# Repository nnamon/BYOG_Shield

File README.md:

# BYOG_Shield
Resources pertaining to the Build Your Own Arduino Shield workshop conducted by [AIS Cube](http://www.aiscube.com) and organised with [12Geeks](https://12geeks.com)

>Follow us on [Facebook](https://www.facebook.com/aiscube.sg)/[Instagram](https://www.instagram.com/aiscube.sg)/[Twitter](https://twitter.com/AIS_Cube) for upcoming public workshops & photos of those we conducted.

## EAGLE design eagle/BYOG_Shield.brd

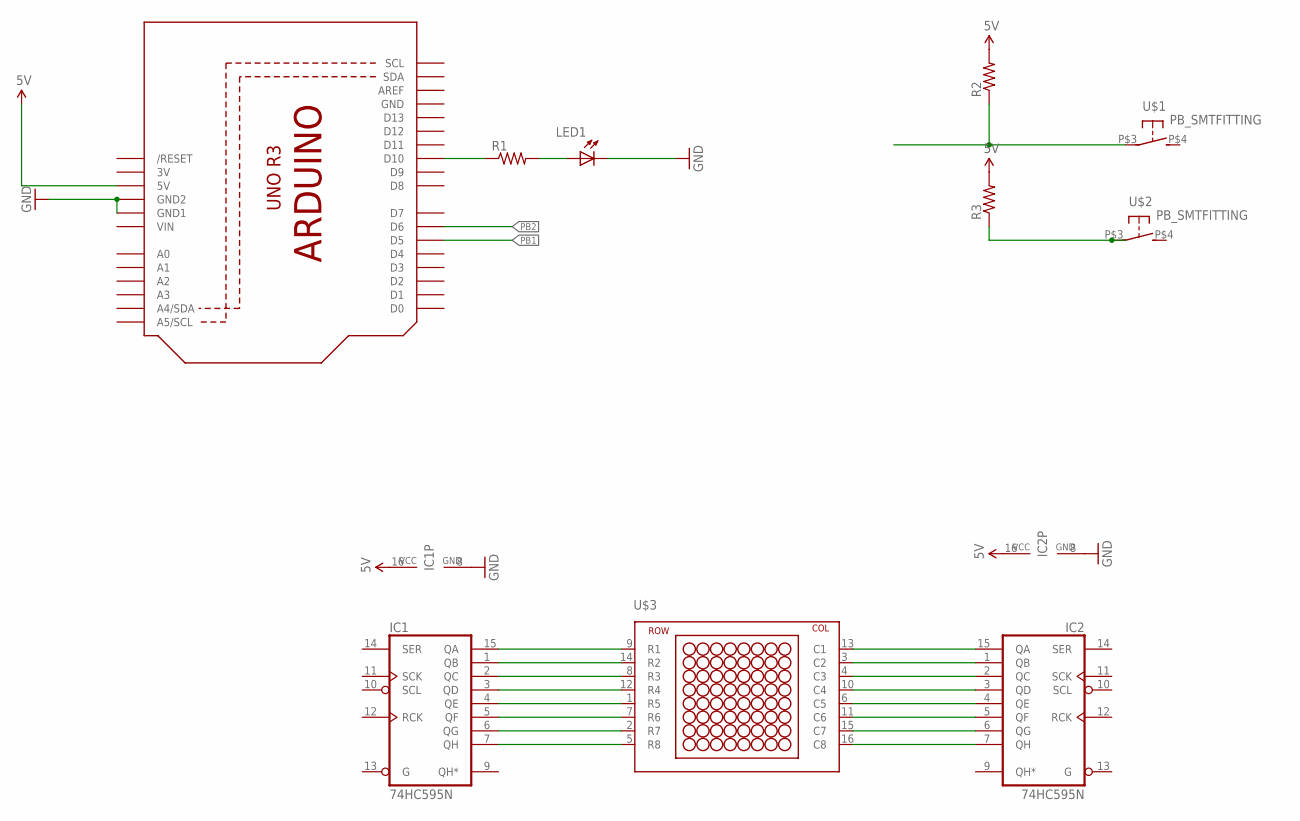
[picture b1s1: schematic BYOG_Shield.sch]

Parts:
IC1, IC2: 74HC595N; DIL16
LED1: LED/0805; CHIP-LED0805
R1, R2, R3: RESISTOR0805-RES; 0805
U1: ARDUINOR3-NOIOREF-NOTEXT; ARDUINOR3-NOTEXT-NOIOREF
U$1, U$2: PB_SMTFITTING; PB_SMT_TIGHT
U$3: 8X8DM_2088AS

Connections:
3V: U1.3V
5V: IC1.16 (VCC), IC2.16 (VCC), R2.2, R3.2, U1.5V
GND: IC1.8 (GND), IC2.8 (GND), LED1.C, U1.GND, U1.GND1, U1.GND2
unnamed: R1.1, U1.D10
unnamed: LED1.A, R1.2
unnamed: R2.1, U$1.P$3 (1)
unnamed: R3.1, U$2.P$3 (1)
unnamed: IC1.1 (QB), U$3.14 (R2)
unnamed: IC1.2 (QC), U$3.8 (R3)
unnamed: IC1.3 (QD), U$3.12 (R4)
unnamed: IC1.4 (QE), U$3.1 (R5)
unnamed: IC1.5 (QF), U$3.7 (R6)
unnamed: IC1.6 (QG), U$3.2 (R7)
unnamed: IC1.7 (QH), U$3.5 (R8)
unnamed: IC1.15 (QA), U$3.9 (R1)
unnamed: IC2.1 (QB), U$3.3 (C2)
unnamed: IC2.2 (QC), U$3.4 (C3)
unnamed: IC2.3 (QD), U$3.10 (C4)
unnamed: IC2.4 (QE), U$3.6 (C5)
unnamed: IC2.5 (QF), U$3.11 (C6)
unnamed: IC2.6 (QG), U$3.15 (C7)
unnamed: IC2.7 (QH), U$3.16 (C8)
unnamed: IC2.15 (QA), U$3.13 (C1)
PB1: U1.D5
PB2: U1.D6
VIN: U1.VIN

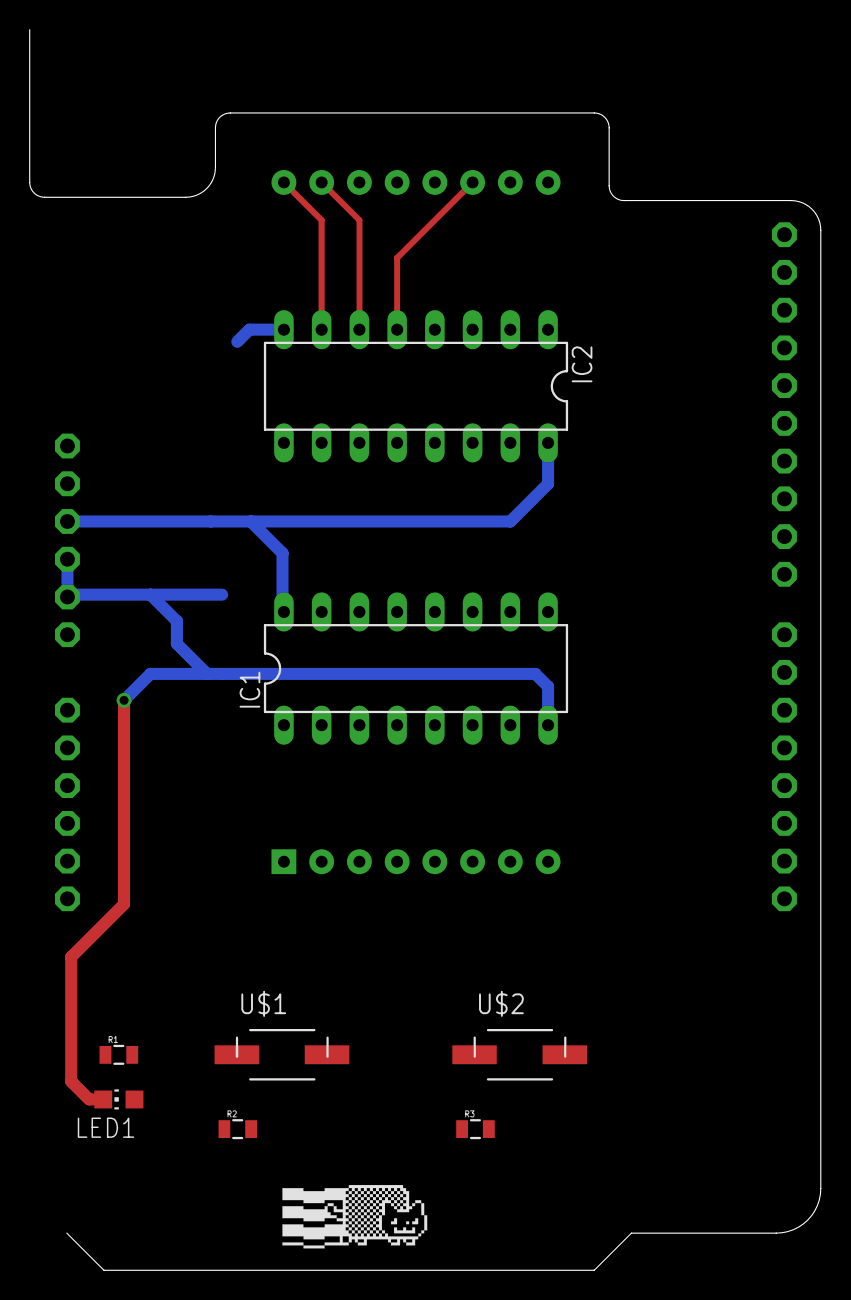
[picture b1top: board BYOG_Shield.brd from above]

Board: 2 copper layers, 53.2 x 83.5 mm, 11 parts (0 on the bottom side), 22 nets.

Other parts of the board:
U$8: LOGO_NYAN

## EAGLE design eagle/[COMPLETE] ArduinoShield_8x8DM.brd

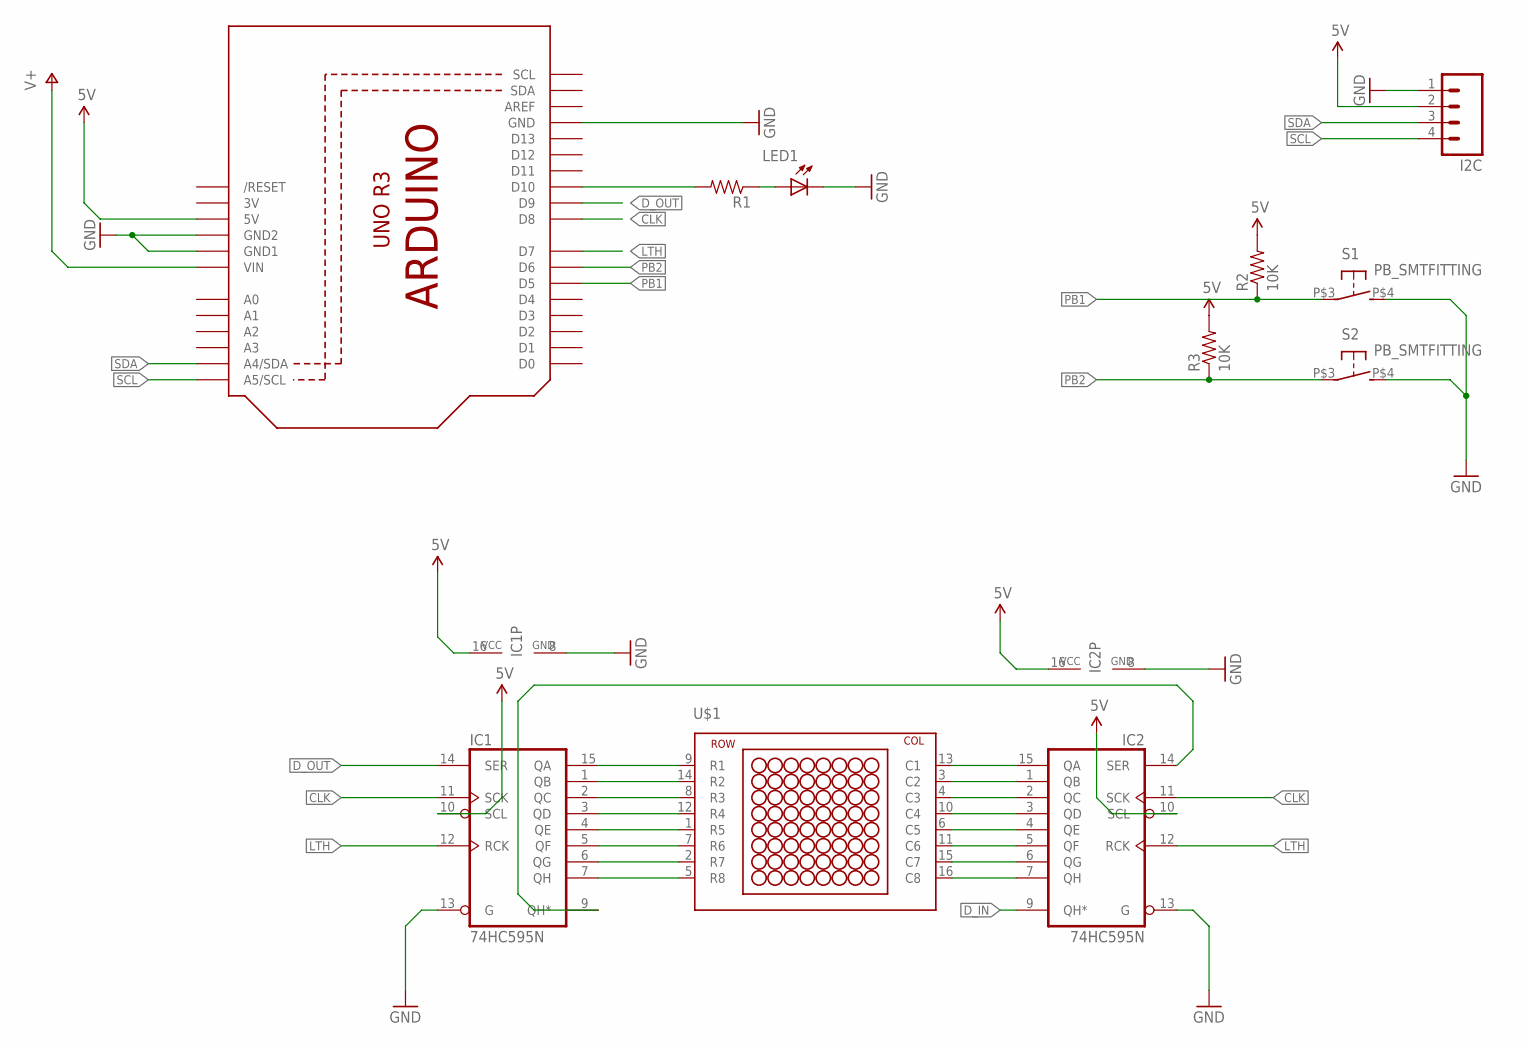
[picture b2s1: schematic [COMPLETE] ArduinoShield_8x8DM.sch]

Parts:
I2C: M04PTH; 1X04
IC1, IC2: 74HC595N; DIL16
LED1: LED/0805; CHIP-LED0805
R1: RESISTOR0805-RES; 0805
R2, R3: 10K; 0805
S1, S2: PB_SMTFITTING; PB_SMT_TIGHT
U1: ARDUINOR3-NOIOREF-NOTEXT; ARDUINOR3-NOTEXT-NOIOREF
U$1: 8X8DM_2088AS

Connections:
3V: U1.3V
5V: I2C.2, IC1.10 (SCL), IC1.16 (VCC), IC2.10 (SCL), IC2.16 (VCC), R2.2, R3.2, U1.5V
CLK: IC1.11 (SCK), IC2.11 (SCK), U1.D8
D_IN: IC2.9 (QH*)
D_OUT: IC1.14 (SER), U1.D9
GND: I2C.1, IC1.8 (GND), IC1.13 (G), IC2.8 (GND), IC2.13 (G), LED1.C, S1.P$4 (2), S2.P$4 (2), U1.GND, U1.GND1, U1.GND2
LTH: IC1.12 (RCK), IC2.12 (RCK), U1.D7
unnamed: IC1.1 (QB), U$1.14 (R2)
unnamed: IC1.2 (QC), U$1.8 (R3)
unnamed: IC1.3 (QD), U$1.12 (R4)
unnamed: IC1.4 (QE), U$1.1 (R5)
unnamed: IC1.5 (QF), U$1.7 (R6)
unnamed: IC1.6 (QG), U$1.2 (R7)
unnamed: IC1.7 (QH), U$1.5 (R8)
unnamed: IC1.15 (QA), U$1.9 (R1)
unnamed: IC2.1 (QB), U$1.3 (C2)
unnamed: IC2.2 (QC), U$1.4 (C3)
unnamed: IC2.3 (QD), U$1.10 (C4)
unnamed: IC2.4 (QE), U$1.6 (C5)
unnamed: IC2.5 (QF), U$1.11 (C6)
unnamed: IC2.6 (QG), U$1.15 (C7)
unnamed: IC2.7 (QH), U$1.16 (C8)
unnamed: IC2.15 (QA), U$1.13 (C1)
unnamed: IC1.9 (QH*), IC2.14 (SER)
unnamed: R1.2, U1.D10
unnamed: LED1.A, R1.1
PB1: R2.1, S1.P$3 (1), U1.D5
PB2: R3.1, S2.P$3 (1), U1.D6
SCL: I2C.4, U1.A5 (A5/SCL)
SDA: I2C.3, U1.A4 (A4/SDA)
V+: U1.VIN

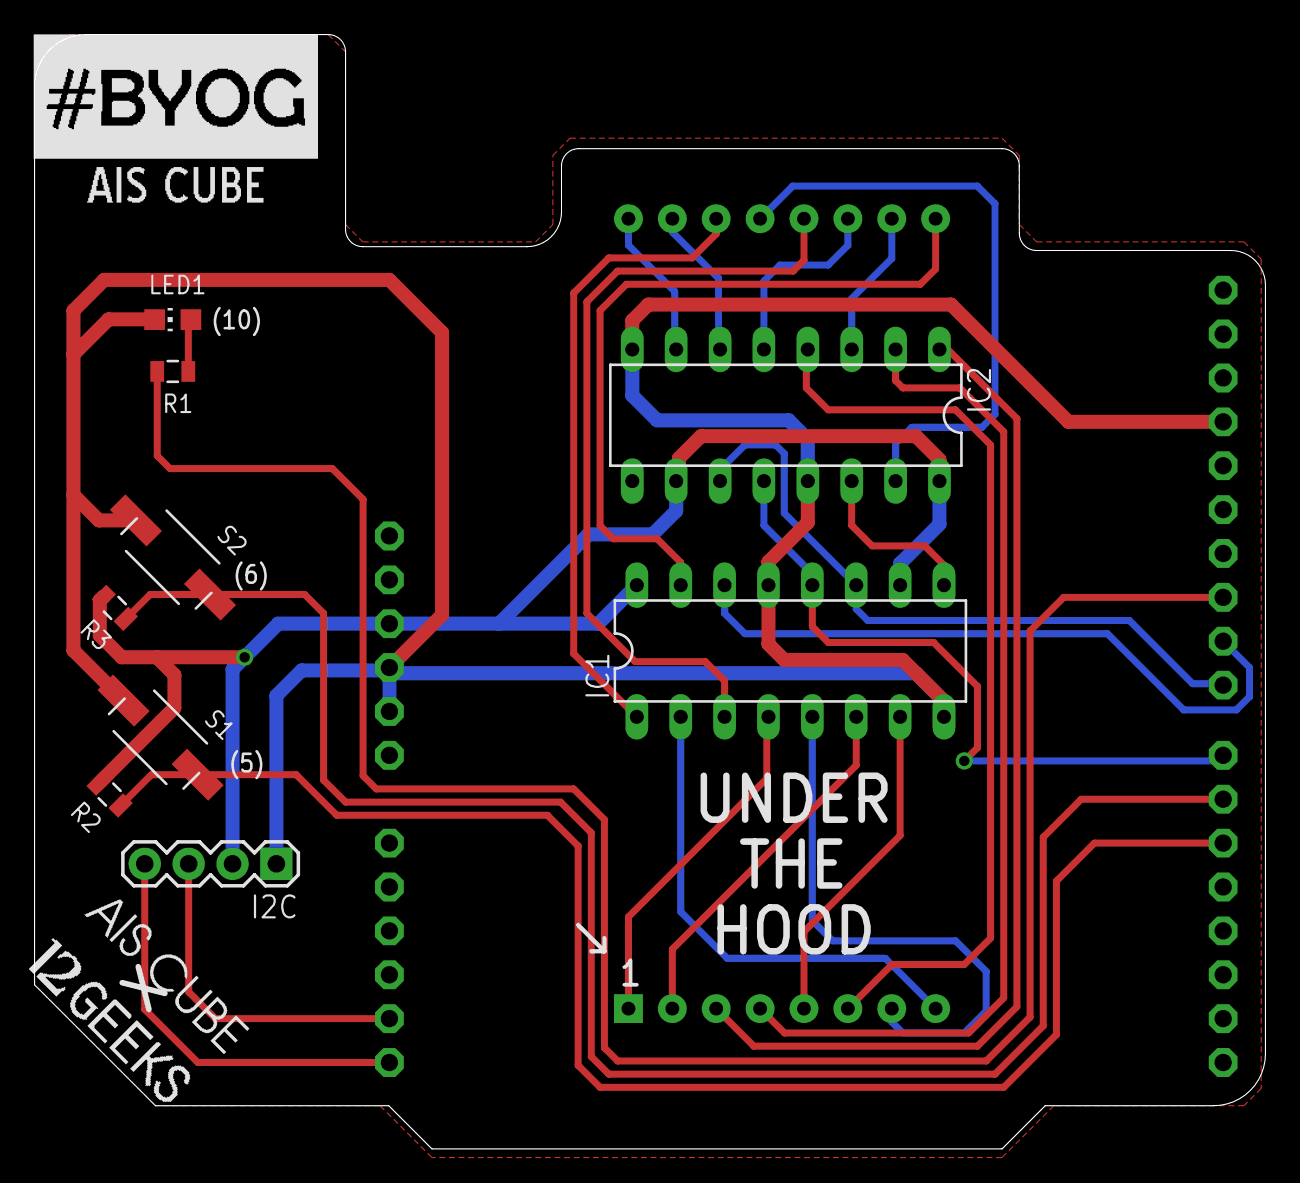
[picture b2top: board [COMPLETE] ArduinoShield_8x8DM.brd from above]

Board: 2 copper layers, 71.2 x 64.5 mm, 14 parts (0 on the bottom side), 28 nets.

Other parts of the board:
U$2: LOGO_17MM
U$8: LOGO_12GEEKS
U$9: AISCUBE_LOGO_S

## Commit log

2016-11-04 :lollipop: Added .gitattributes & .gitignore files
2016-11-04 Session 1 Resources Added
    Added Arduino Program Examples & Notes for Session 1 of the Build Your
    Own Arduino Shield - PCB workshop organised by 12Geeks & AISCube
2016-11-05 Added in EAGLE resources
2016-11-06 Updated slides to include introduction to EAGLE
2016-11-11 Added in Slides & EAGLE files for Session 2
2016-11-13 COMPLETE & EXPRESS versions of PCB files added
    Added in EXPRESS and COMPLETE version of the EAGLE files to
    complete/refer to.
    Use EXPRESS to jumpstart the routing task. Good luck and have fun!
